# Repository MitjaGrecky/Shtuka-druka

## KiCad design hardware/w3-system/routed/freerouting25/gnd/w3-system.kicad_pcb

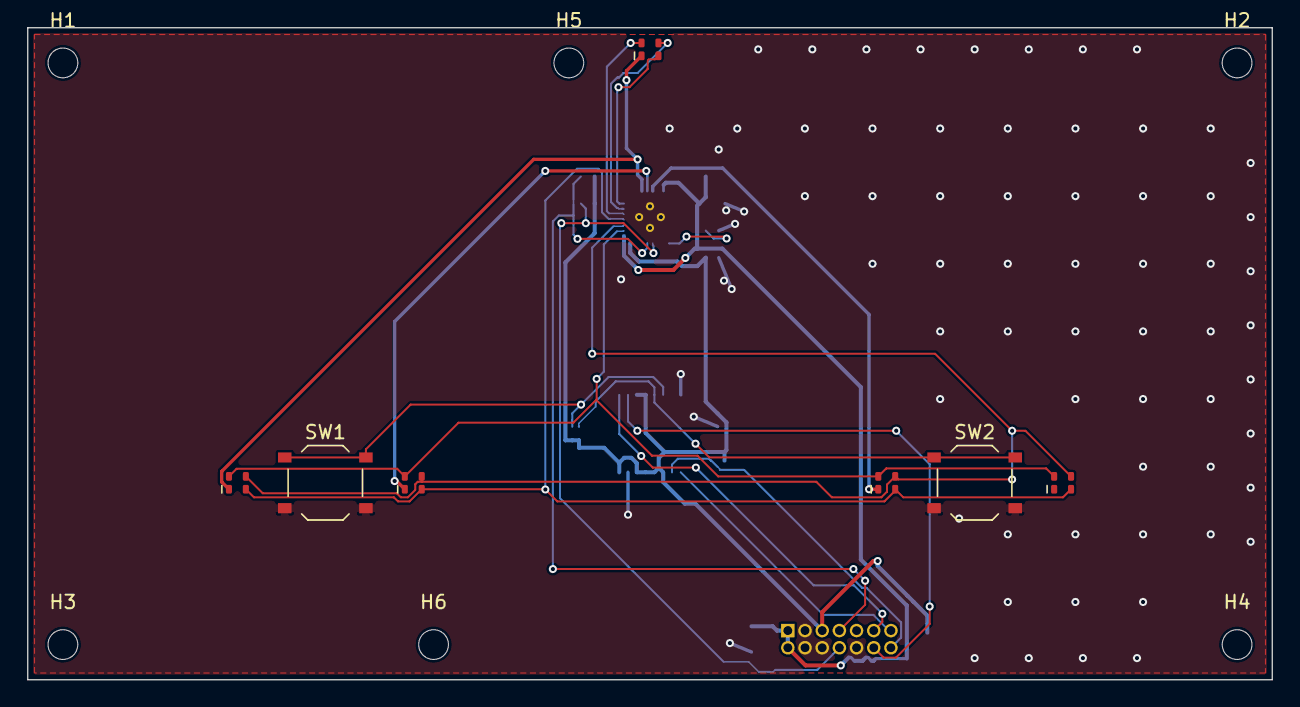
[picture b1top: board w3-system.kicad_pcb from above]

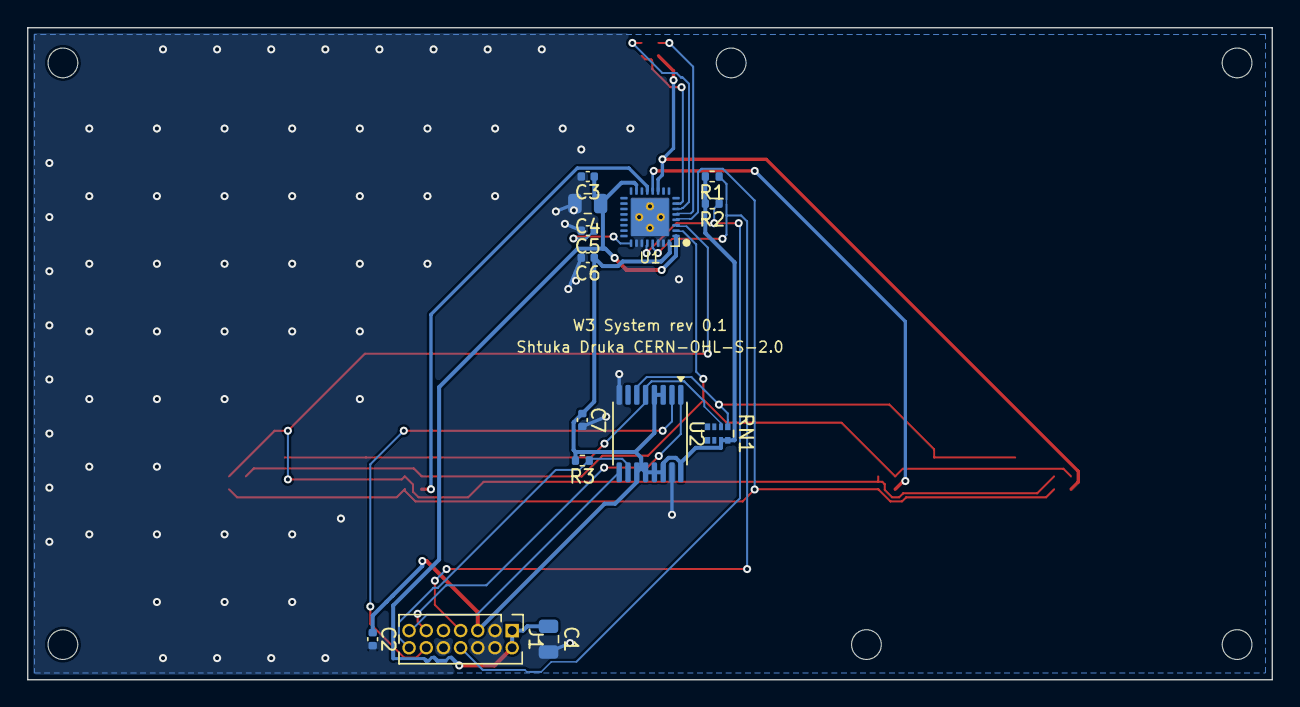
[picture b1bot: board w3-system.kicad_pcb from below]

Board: 2 copper layers, 92.0 x 48.2 mm, 27 parts (14 on the bottom side), 22 nets.

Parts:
C1: 10u; C_0805_2012Metric
C2, C3, C5: 1u; C_0402_1005Metric
C4: 4.7u; C_0805_2012Metric
C6: 1n; C_0402_1005Metric
C7: 100n; C_0402_1005Metric
D1, D2, D3, D4, D5: XL-1615RGBC-RF; LED_RGB_XL-1615RGBC_1.6x1.5mm
H1, H2, H3, H4, H5, H6: M2; MountingHole_2.2mm_M2
J1: Module bus 2x7 1.27; PinHeader_2x07_P1.27mm_Vertical
R1, R2: 4.7k; R_0402_1005Metric
R3: 10k; R_0402_1005Metric
RN1: 4x10k; R_Array_Convex_4x0402
SW1, SW2: TS-1187A-B-A-B; SW_Push_1P1T_XKB_TS-1187A
U1: LP5864RSMR; VQFN-32-1EP_4x4mm_P0.4mm_EP2.8x2.8mm
U2: 74HC165PW; TSSOP-16_4.4x5mm_P0.65mm

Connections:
+3V3: C2.1, C6.1, C7.1, J1.5, R1.2, R2.2, R3.2, RN1.7, RN1.8, U1.32, U2.3, U2.4, U2.11, U2.12, U2.13, U2.14, U2.16
+5V: C1.1, C3.1, C4.1, J1.1, J1.2, U1.1, U1.15
/A_CS0: D1.1, D2.1, D3.1, D4.1, U1.2
/A_CS1: D1.3, D2.3, D3.3, D4.3, U1.3
/A_CS2: D1.4, D2.4, D3.4, D4.4, U1.4
/A_CS3: D5.1, U1.5
/A_CS4: D5.3, U1.6
/A_CS5: D5.4, U1.7
/A_SW0: D1.2, D5.2, U1.11
/A_SW1: D2.2, U1.12
/A_SW2: D3.2, U1.13
/A_SW3: D4.2, U1.14
/A_VCAP: C5.1, U1.25
/BTN_PROJECT: RN1.2, SW2.1, U2.5
/BTN_SAVE: RN1.1, SW1.1, U2.6
/SCL: J1.8, R2.1, U1.28
/SDA: J1.7, R1.1, U1.29
/SR_CLK: J1.12, U2.2
/SR_IN: J1.14, R3.1, U2.10
/SR_OUT: J1.13, U2.9
/~SR_LOAD: J1.11, U2.1
GND: C1.2, C2.2, C3.2, C4.2, C5.2, C6.2, C7.2, J1.3, J1.4, J1.6, J1.10, SW1.2, SW2.2, U1.26, U1.27, U1.30, U1.31, U1.33, U2.8, U2.15

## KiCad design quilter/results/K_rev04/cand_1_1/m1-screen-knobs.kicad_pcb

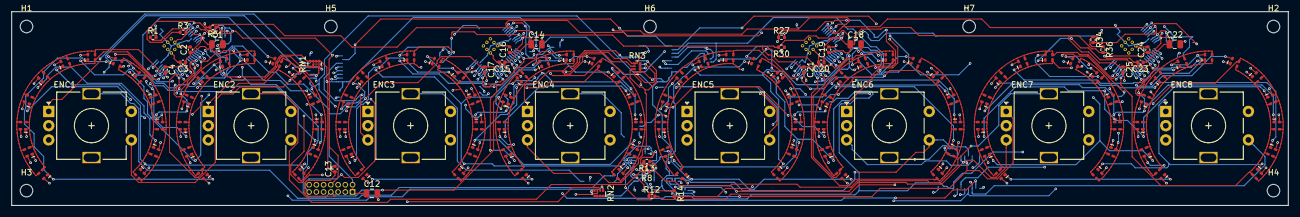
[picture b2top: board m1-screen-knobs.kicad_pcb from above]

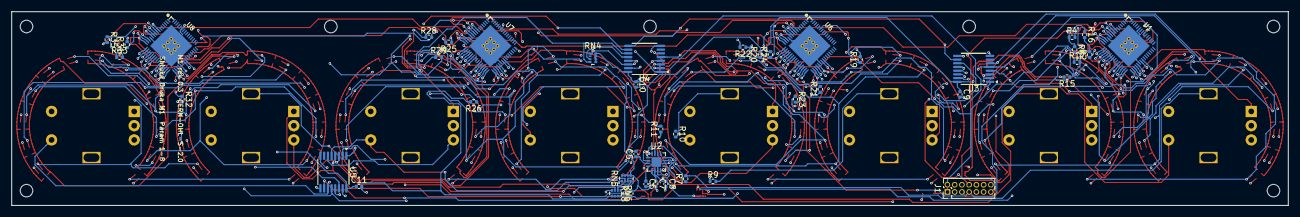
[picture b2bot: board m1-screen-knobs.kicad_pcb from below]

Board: 4 copper layers, 224.0 x 34.0 mm, 195 parts (44 on the bottom side), 142 nets.

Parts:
C1, C14, C18, C22: 4.7u; C_0805_2012Metric
C2, C7, C13, C15, C19, C23: 1u; C_0402_1005Metric
C3, C4, C6, C8, C9, C10, C11, C16, C17, C20, C21, C24, C25: 100n; C_0402_1005Metric
C5: 2.2n; C_0402_1005Metric
C12: 10u; C_0805_2012Metric
D1, D2, D3, D4, D5, D6, D7, D8, D9, D10, D11, D12, D13, D14, D15, D16, D17, D18, D19, D20, D21, D22, D23, D24, D25, D26, D27, D28, D29, D30, D31, D32, D33, D34, D35, D36, D37, D38, D39, D40, D41, D42, D43, D44, D45, D46, D47, D48, D49, D50, D51, D52, D53, D54, D55, D56, D57, D58, D59, D60, D61, D62, D63, D64, D65, D66, D67, D68, D69, D70, D71, D72, D73, D74, D75, D76, D77, D78, D79, D80, D81, D82, D83, D84, D85, D86, D87, D88, D89, D90, D91, D92, D93, D94, D95, D96, D97, D98, D99, D100, D101, D102, D103, D104: XL-1615RGBC-RF; LED_RGB_XL-1615RGBC_1.6x1.5mm
ENC1, ENC2, ENC3, ENC4, ENC5, ENC6, ENC7, ENC8: EC11E smooth, switch; RotaryEncoder_Alps_EC11E-Switch_Vertical_H20mm_Ring
H1, H2, H3, H4, H5, H6, H7: M2; MountingHole_2.2mm_M2
J1: Module bus 2x7 1.27; PinHeader_2x07_P1.27mm_Vertical
R1, R19, R25, R31: 20k 1%; R_0402_1005Metric
R2, R17, R18, R20, R26, R32: 10k; R_0402_1005Metric
R3, R4, R5, R6, R21, R22, R23, R24, R27, R28, R29, R30, R33, R34, R35, R36: 0; R_0402_1005Metric
R7, R8, R9, R10, R11, R12, R13, R14: 560; R_0402_1005Metric
R15, R16: 4.7k; R_0402_1005Metric
RN1, RN2, RN3, RN4, RN5, RN6: 4x10k; R_Array_Convex_4x0402
U1, U6, U7, U8: IS31FL3741A-QFLS4-TR; QFN-60-1EP_7x7mm_P0.4mm_EP5.25x5.25mm
U2: CY8CMBR3108-LQXIT; QFN-16-1EP_3x3mm_P0.5mm_EP1.7x1.7mm
U3, U4, U5: 74HC165PW; TSSOP-16_4.4x5mm_P0.65mm

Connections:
+3V3: C7.1, C8.1, C9.1, C10.1, C11.1, C13.1, J1.5, R2.2, R15.2, R16.2, R17.2, R18.2, R20.2, R26.2, R32.2, RN1.5, RN1.6, RN1.7, RN1.8, RN2.5, RN2.6, RN2.7, RN2.8, RN3.5, RN3.6, RN3.7, RN3.8, RN4.5, RN4.6, RN4.7, RN4.8, RN5.5, RN5.6, RN5.7, RN5.8, RN6.5, RN6.6, RN6.7, RN6.8, U2.5, U2.6, U3.16, U4.16, U5.16
+5V: C1.1, C2.1, C3.1, C4.1, C12.1, C14.1, C15.1, C16.1, C17.1, C18.1, C19.1, C20.1, C21.1, C22.1, C23.1, C24.1, C25.1, J1.1, J1.2, R6.2, R24.2, R30.2, R36.2, U1.14, U1.15, U1.25, U6.14, U6.15, U6.25, U7.14, U7.15, U7.25, U8.14, U8.15, U8.25
/A_ADDR: R3.1, R4.1, R5.1, R6.1, U1.8
/A_CS1: D14.1, D15.1, D16.1, D17.1, D18.1, D19.1, D20.1, U1.26
/A_CS2: D14.3, D15.3, D16.3, D17.3, D18.3, D19.3, D20.3, U1.27
/A_CS3: D14.4, D15.4, D16.4, D17.4, D18.4, D19.4, D20.4, U1.28
/A_CS4: D21.1, D22.1, D23.1, D24.1, D25.1, D26.1, U1.29
/A_CS5: D21.3, D22.3, D23.3, D24.3, D25.3, D26.3, U1.30
/A_CS6: D21.4, D22.4, D23.4, D24.4, D25.4, D26.4, U1.31
/A_CS7: D1.1, D2.1, D3.1, D4.1, D5.1, D6.1, D7.1, U1.32
/A_CS8: D1.3, D2.3, D3.3, D4.3, D5.3, D6.3, D7.3, U1.33
/A_CS9: D1.4, D2.4, D3.4, D4.4, D5.4, D6.4, D7.4, U1.34
/A_CS10: D8.1, D9.1, D10.1, D11.1, D12.1, D13.1, U1.35
/A_CS11: D8.3, D9.3, D10.3, D11.3, D12.3, D13.3, U1.37
/A_CS12: D8.4, D9.4, D10.4, D11.4, D12.4, D13.4, U1.38
/A_REXT: R1.1, U1.13
/A_SDB: R2.1, U1.11
/A_SW1: D1.2, D8.2, D14.2, D21.2, U1.16
/A_SW2: D2.2, D9.2, D15.2, D22.2, U1.17
/A_SW3: D3.2, D10.2, D16.2, D23.2, U1.18
/A_SW4: D4.2, D11.2, D17.2, D24.2, U1.19
/A_SW5: D5.2, D12.2, D18.2, D25.2, U1.20
/A_SW6: D6.2, D13.2, D19.2, D26.2, U1.21
/A_SW7: D7.2, D20.2, U1.22
/B_ADDR: R21.1, R22.1, R23.1, R24.1, U6.8
/B_CS1: D40.1, D41.1, D42.1, D43.1, D44.1, D45.1, D46.1, U6.26
/B_CS2: D40.3, D41.3, D42.3, D43.3, D44.3, D45.3, D46.3, U6.27
/B_CS3: D40.4, D41.4, D42.4, D43.4, D44.4, D45.4, D46.4, U6.28
/B_CS4: D47.1, D48.1, D49.1, D50.1, D51.1, D52.1, U6.29
/B_CS5: D47.3, D48.3, D49.3, D50.3, D51.3, D52.3, U6.30
/B_CS6: D47.4, D48.4, D49.4, D50.4, D51.4, D52.4, U6.31
/B_CS7: D27.1, D28.1, D29.1, D30.1, D31.1, D32.1, D33.1, U6.32
/B_CS8: D27.3, D28.3, D29.3, D30.3, D31.3, D32.3, D33.3, U6.33
/B_CS9: D27.4, D28.4, D29.4, D30.4, D31.4, D32.4, D33.4, U6.34
/B_CS10: D34.1, D35.1, D36.1, D37.1, D38.1, D39.1, U6.35
/B_CS11: D34.3, D35.3, D36.3, D37.3, D38.3, D39.3, U6.37
/B_CS12: D34.4, D35.4, D36.4, D37.4, D38.4, D39.4, U6.38
/B_REXT: R19.1, U6.13
/B_SDB: R20.1, U6.11
/B_SW1: D27.2, D34.2, D40.2, D47.2, U6.16
/B_SW2: D28.2, D35.2, D41.2, D48.2, U6.17
/B_SW3: D29.2, D36.2, D42.2, D49.2, U6.18
/B_SW4: D30.2, D37.2, D43.2, D50.2, U6.19
/B_SW5: D31.2, D38.2, D44.2, D51.2, U6.20
/B_SW6: D32.2, D39.2, D45.2, D52.2, U6.21
/B_SW7: D33.2, D46.2, U6.22
/CMOD: C5.1, U2.3
/C_ADDR: R27.1, R28.1, R29.1, R30.1, U7.8
/C_CS1: D66.1, D67.1, D68.1, D69.1, D70.1, D71.1, D72.1, U7.26
/C_CS2: D66.3, D67.3, D68.3, D69.3, D70.3, D71.3, D72.3, U7.27
/C_CS3: D66.4, D67.4, D68.4, D69.4, D70.4, D71.4, D72.4, U7.28
/C_CS4: D73.1, D74.1, D75.1, D76.1, D77.1, D78.1, U7.29
/C_CS5: D73.3, D74.3, D75.3, D76.3, D77.3, D78.3, U7.30
/C_CS6: D73.4, D74.4, D75.4, D76.4, D77.4, D78.4, U7.31
/C_CS7: D53.1, D54.1, D55.1, D56.1, D57.1, D58.1, D59.1, U7.32
/C_CS8: D53.3, D54.3, D55.3, D56.3, D57.3, D58.3, D59.3, U7.33
/C_CS9: D53.4, D54.4, D55.4, D56.4, D57.4, D58.4, D59.4, U7.34
/C_CS10: D60.1, D61.1, D62.1, D63.1, D64.1, D65.1, U7.35
/C_CS11: D60.3, D61.3, D62.3, D63.3, D64.3, D65.3, U7.37
/C_CS12: D60.4, D61.4, D62.4, D63.4, D64.4, D65.4, U7.38
/C_REXT: R25.1, U7.13
/C_SDB: R26.1, U7.11
/C_SW1: D53.2, D60.2, D66.2, D73.2, U7.16
/C_SW2: D54.2, D61.2, D67.2, D74.2, U7.17
/C_SW3: D55.2, D62.2, D68.2, D75.2, U7.18
/C_SW4: D56.2, D63.2, D69.2, D76.2, U7.19
/C_SW5: D57.2, D64.2, D70.2, D77.2, U7.20
/C_SW6: D58.2, D65.2, D71.2, D78.2, U7.21
/C_SW7: D59.2, D72.2, U7.22
/D_ADDR: R33.1, R34.1, R35.1, R36.1, U8.8
/D_CS1: D92.1, D93.1, D94.1, D95.1, D96.1, D97.1, D98.1, U8.26
/D_CS2: D92.3, D93.3, D94.3, D95.3, D96.3, D97.3, D98.3, U8.27
/D_CS3: D92.4, D93.4, D94.4, D95.4, D96.4, D97.4, D98.4, U8.28
/D_CS4: D99.1, D100.1, D101.1, D102.1, D103.1, D104.1, U8.29
/D_CS5: D99.3, D100.3, D101.3, D102.3, D103.3, D104.3, U8.30
/D_CS6: D99.4, D100.4, D101.4, D102.4, D103.4, D104.4, U8.31
/D_CS7: D79.1, D80.1, D81.1, D82.1, D83.1, D84.1, D85.1, U8.32
/D_CS8: D79.3, D80.3, D81.3, D82.3, D83.3, D84.3, D85.3, U8.33
/D_CS9: D79.4, D80.4, D81.4, D82.4, D83.4, D84.4, D85.4, U8.34
/D_CS10: D86.1, D87.1, D88.1, D89.1, D90.1, D91.1, U8.35
/D_CS11: D86.3, D87.3, D88.3, D89.3, D90.3, D91.3, U8.37
/D_CS12: D86.4, D87.4, D88.4, D89.4, D90.4, D91.4, U8.38
/D_REXT: R31.1, U8.13
/D_SDB: R32.1, U8.11
/D_SW1: D79.2, D86.2, D92.2, D99.2, U8.16
/D_SW2: D80.2, D87.2, D93.2, D100.2, U8.17
/D_SW3: D81.2, D88.2, D94.2, D101.2, U8.18
/D_SW4: D82.2, D89.2, D95.2, D102.2, U8.19
/D_SW5: D83.2, D90.2, D96.2, D103.2, U8.20
/D_SW6: D84.2, D91.2, D97.2, D104.2, U8.21
/D_SW7: D85.2, D98.2, U8.22
/E0_A: ENC1.A, RN1.1, U3.6
/E0_B: ENC1.B, RN1.2, U3.5
/E0_SW: ENC1.S1, RN1.3, U3.4
/E1_A: ENC2.A, RN1.4, U3.3
/E1_B: ENC2.B, RN2.1, U3.14
/E1_SW: ENC2.S1, RN2.2, U3.13
/E2_A: ENC3.A, RN2.3, U3.12
/E2_B: ENC3.B, RN2.4, U3.11
/E2_SW: ENC3.S1, RN3.1, U4.6
/E3_A: ENC4.A, RN3.2, U4.5
/E3_B: ENC4.B, RN3.3, U4.4
/E3_SW: ENC4.S1, RN3.4, U4.3
/E4_A: ENC5.A, RN4.1, U4.14
/E4_B: ENC5.B, RN4.2, U4.13
/E4_SW: ENC5.S1, RN4.3, U4.12
/E5_A: ENC6.A, RN4.4, U4.11
/E5_B: ENC6.B, RN5.1, U5.6
/E5_SW: ENC6.S1, RN5.2, U5.5
/E6_A: ENC7.A, RN5.3, U5.4
/E6_B: ENC7.B, RN5.4, U5.3
/E6_SW: ENC7.S1, RN6.1, U5.14
/E7_A: ENC8.A, RN6.2, U5.13
/E7_B: ENC8.B, RN6.3, U5.12
/E7_SW: ENC8.S1, RN6.4, U5.11
/SCL: J1.8, R4.2, R16.1, R22.2, R28.2, R34.2, U1.10, U2.15, U6.10, U7.10, U8.10
/SDA: J1.7, R5.2, R15.1, R23.2, R29.2, R35.2, U1.9, U2.14, U6.9, U7.9, U8.9
/SR_CLK: J1.12, U3.2, U4.2, U5.2
/SR_IN: J1.14, R18.1, U5.10
/SR_OUT: J1.13, U3.9
/SR_Q3: U3.10, U4.9
/SR_Q4: U4.10, U5.9
/TOUCH0: ENC1.MP, R7.2
/TOUCH1: ENC2.MP, R8.2
/TOUCH2: ENC3.MP, R9.2
/TOUCH3: ENC4.MP, R10.2
/TOUCH4: ENC5.MP, R11.2
/TOUCH5: ENC6.MP, R12.2
/TOUCH6: ENC7.MP, R13.2
/TOUCH7: ENC8.MP, R14.2
/TR0: R7.1, U2.1
/TR1: R8.1, U2.2
/TR2: R9.1, U2.12
/TR3: R10.1, U2.13
/TR4: R11.1, U2.8
/TR5: R12.1, U2.9
/TR6: R13.1, U2.10
/TR7: R14.1, U2.11
/VREG: C6.1, U2.4
/~INT: J1.9, R17.1, U1.7, U2.16, U6.7, U7.7, U8.7
/~SR_LOAD: J1.11, U3.1, U4.1, U5.1
GND: C1.2, C2.2, C3.2, C4.2, C5.2, C6.2, C7.2, C8.2, C9.2, C10.2, C11.2, C12.2, C13.2, C14.2, C15.2, C16.2, C17.2, C18.2, C19.2, C20.2, C21.2, C22.2, C23.2, C24.2, C25.2, ENC1.C, ENC1.S2, ENC2.C, ENC2.S2, ENC3.C, ENC3.S2, ENC4.C, ENC4.S2, ENC5.C, ENC5.S2, ENC6.C, ENC6.S2, ENC7.C, ENC7.S2, ENC8.C, ENC8.S2, J1.3, J1.4, J1.6, J1.10, R1.2, R3.2, R19.2, R21.2, R25.2, R27.2, R31.2, R33.2, U1.12, U1.36, U1.55, U1.61, U2.7, U2.17, U3.8, U3.15, U4.8, U4.15, U5.8, U5.15, U6.12, U6.36, U6.55, U6.61, U7.12, U7.36, U7.55, U7.61, U8.12, U8.36, U8.55, U8.61

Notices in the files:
hardware/w3-system/routed/freerouting25/gnd/w3-system.kicad_pcb:
Shtuka Druka - open hardware, CERN-OHL-S-2.0
Shtuka Druka CERN-OHL-S-2.0
quilter/results/K_rev04/cand_1_1/m1-screen-knobs.kicad_pcb:
M1 rev 0.3  CERN-OHL-S-2.0
